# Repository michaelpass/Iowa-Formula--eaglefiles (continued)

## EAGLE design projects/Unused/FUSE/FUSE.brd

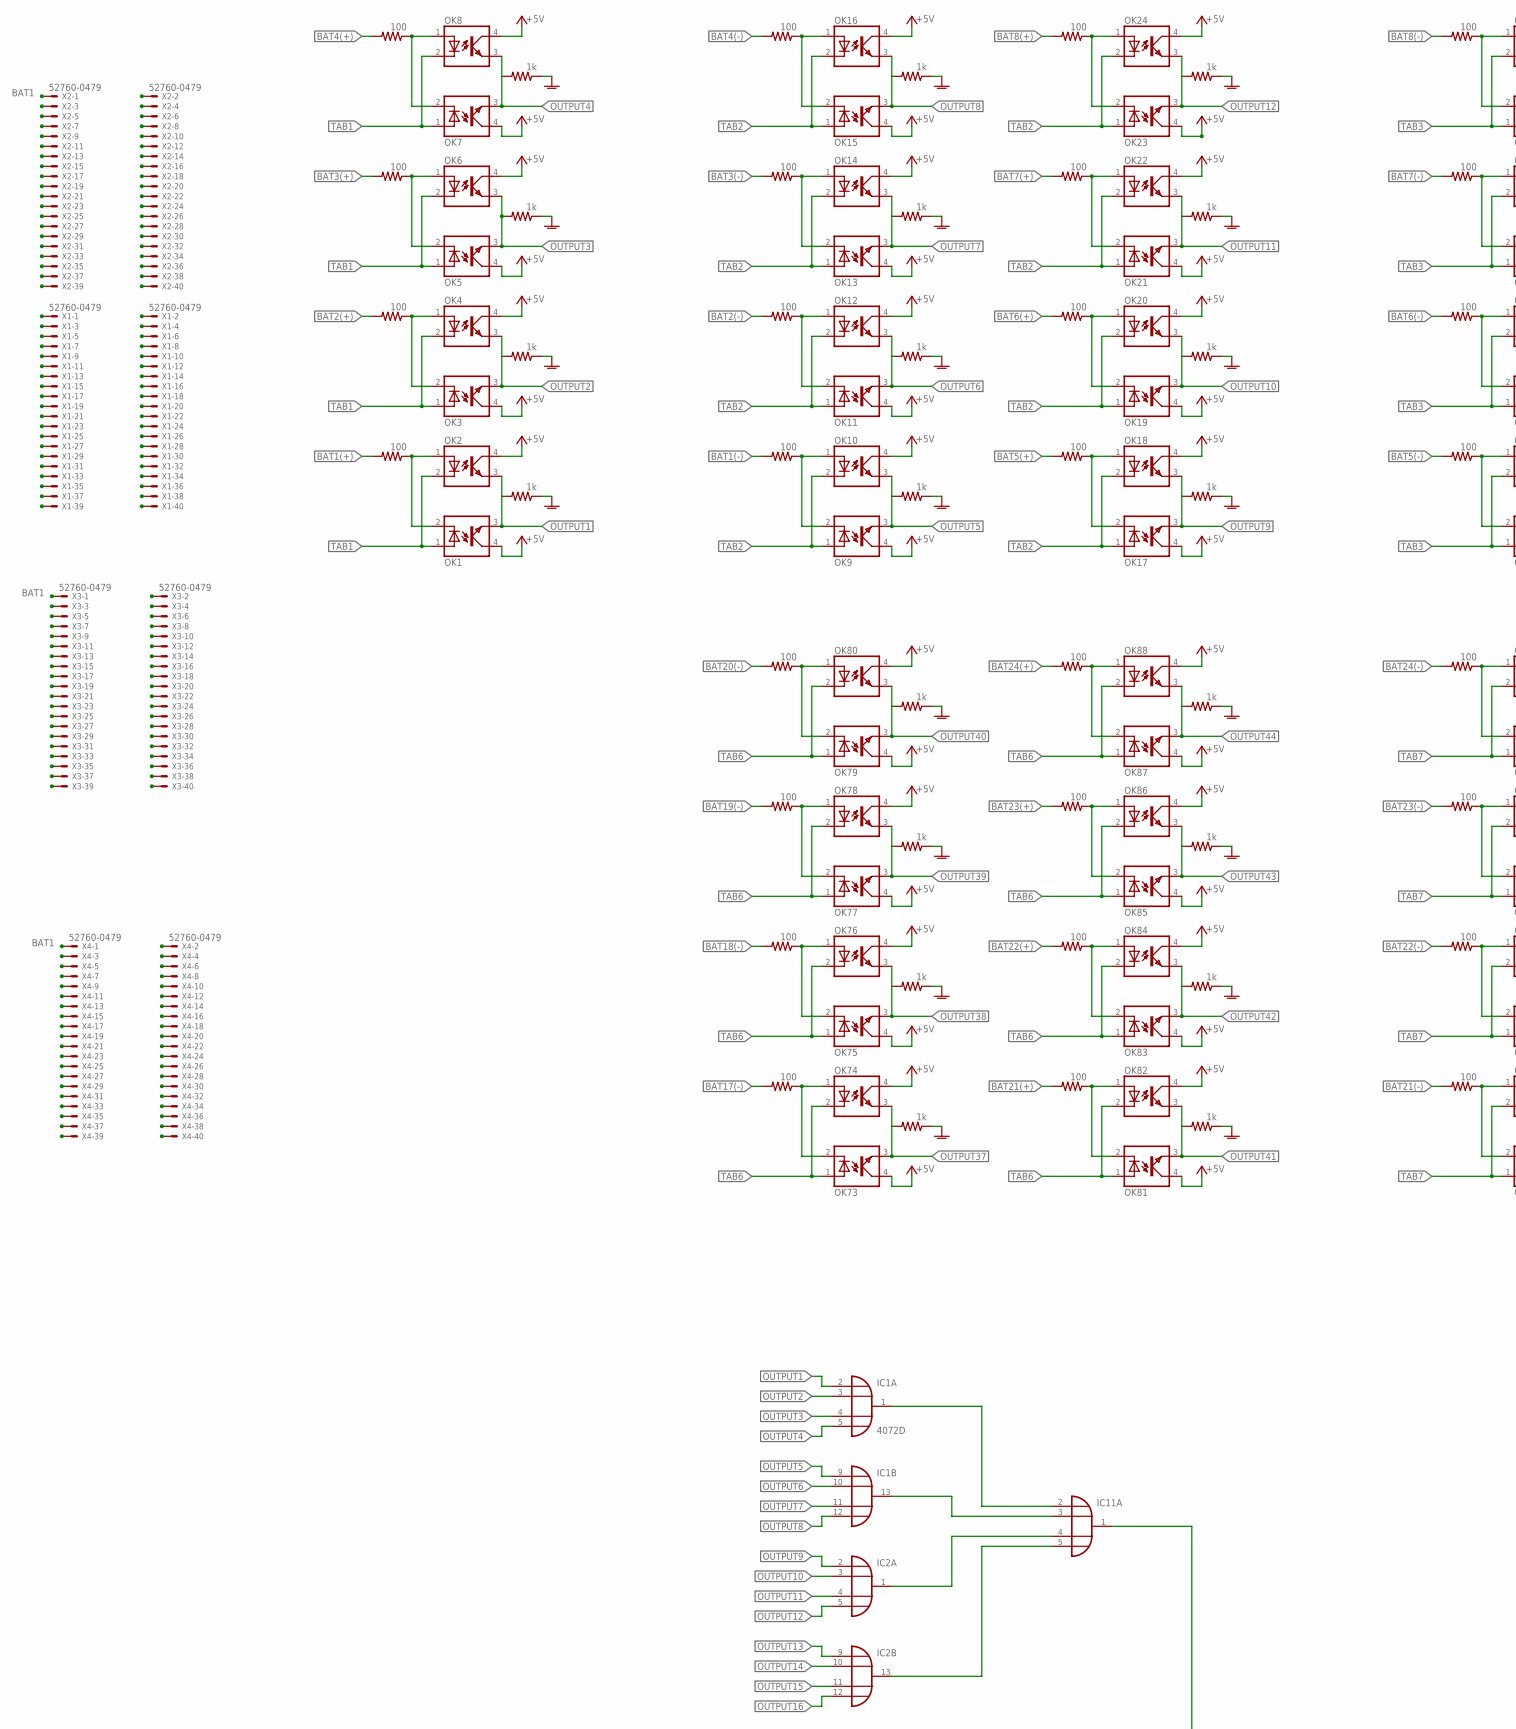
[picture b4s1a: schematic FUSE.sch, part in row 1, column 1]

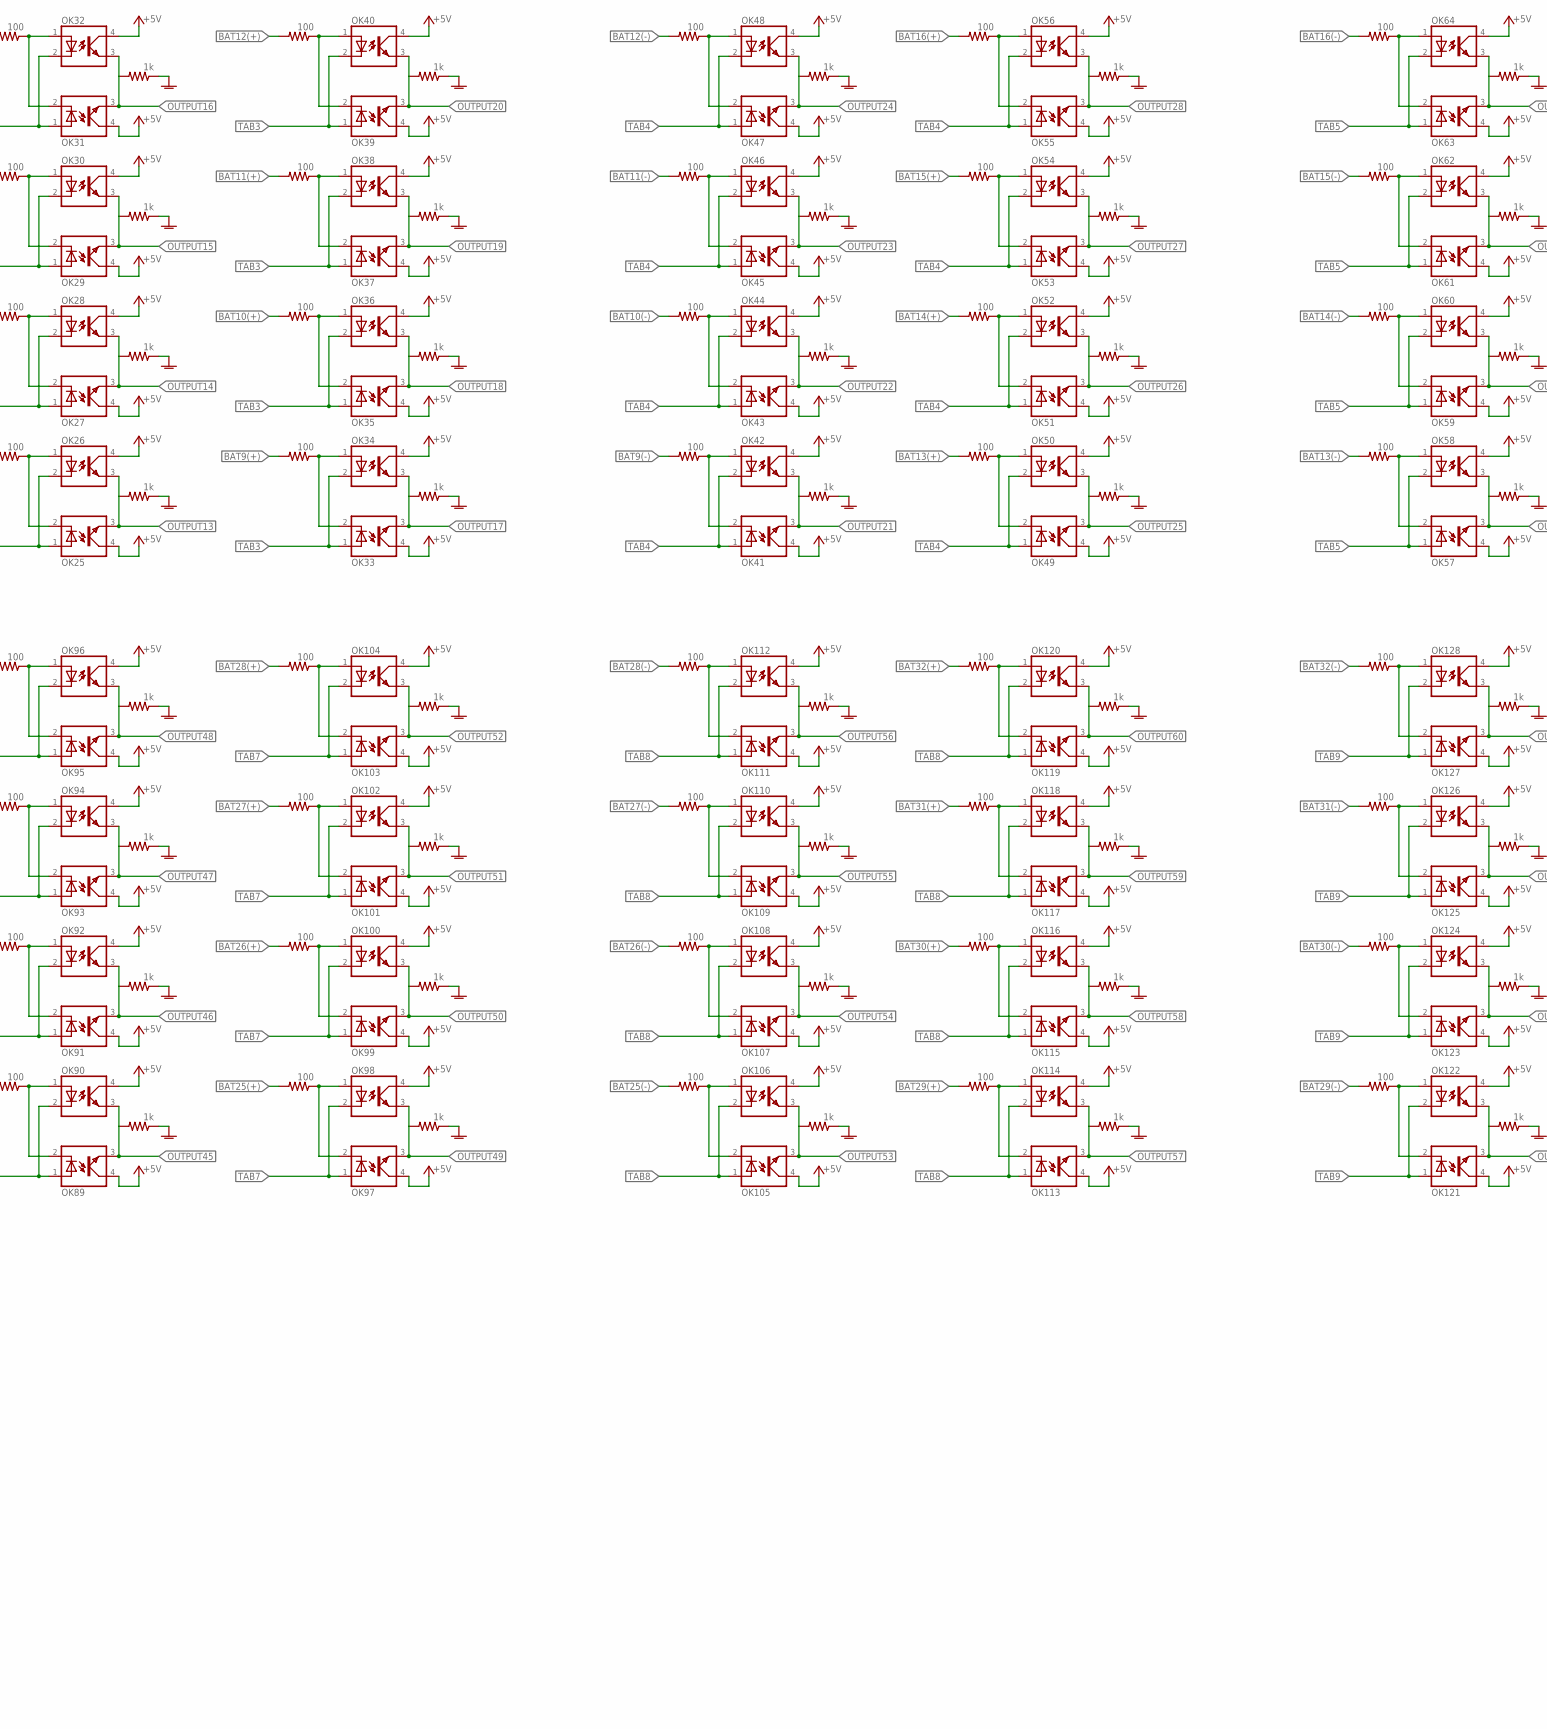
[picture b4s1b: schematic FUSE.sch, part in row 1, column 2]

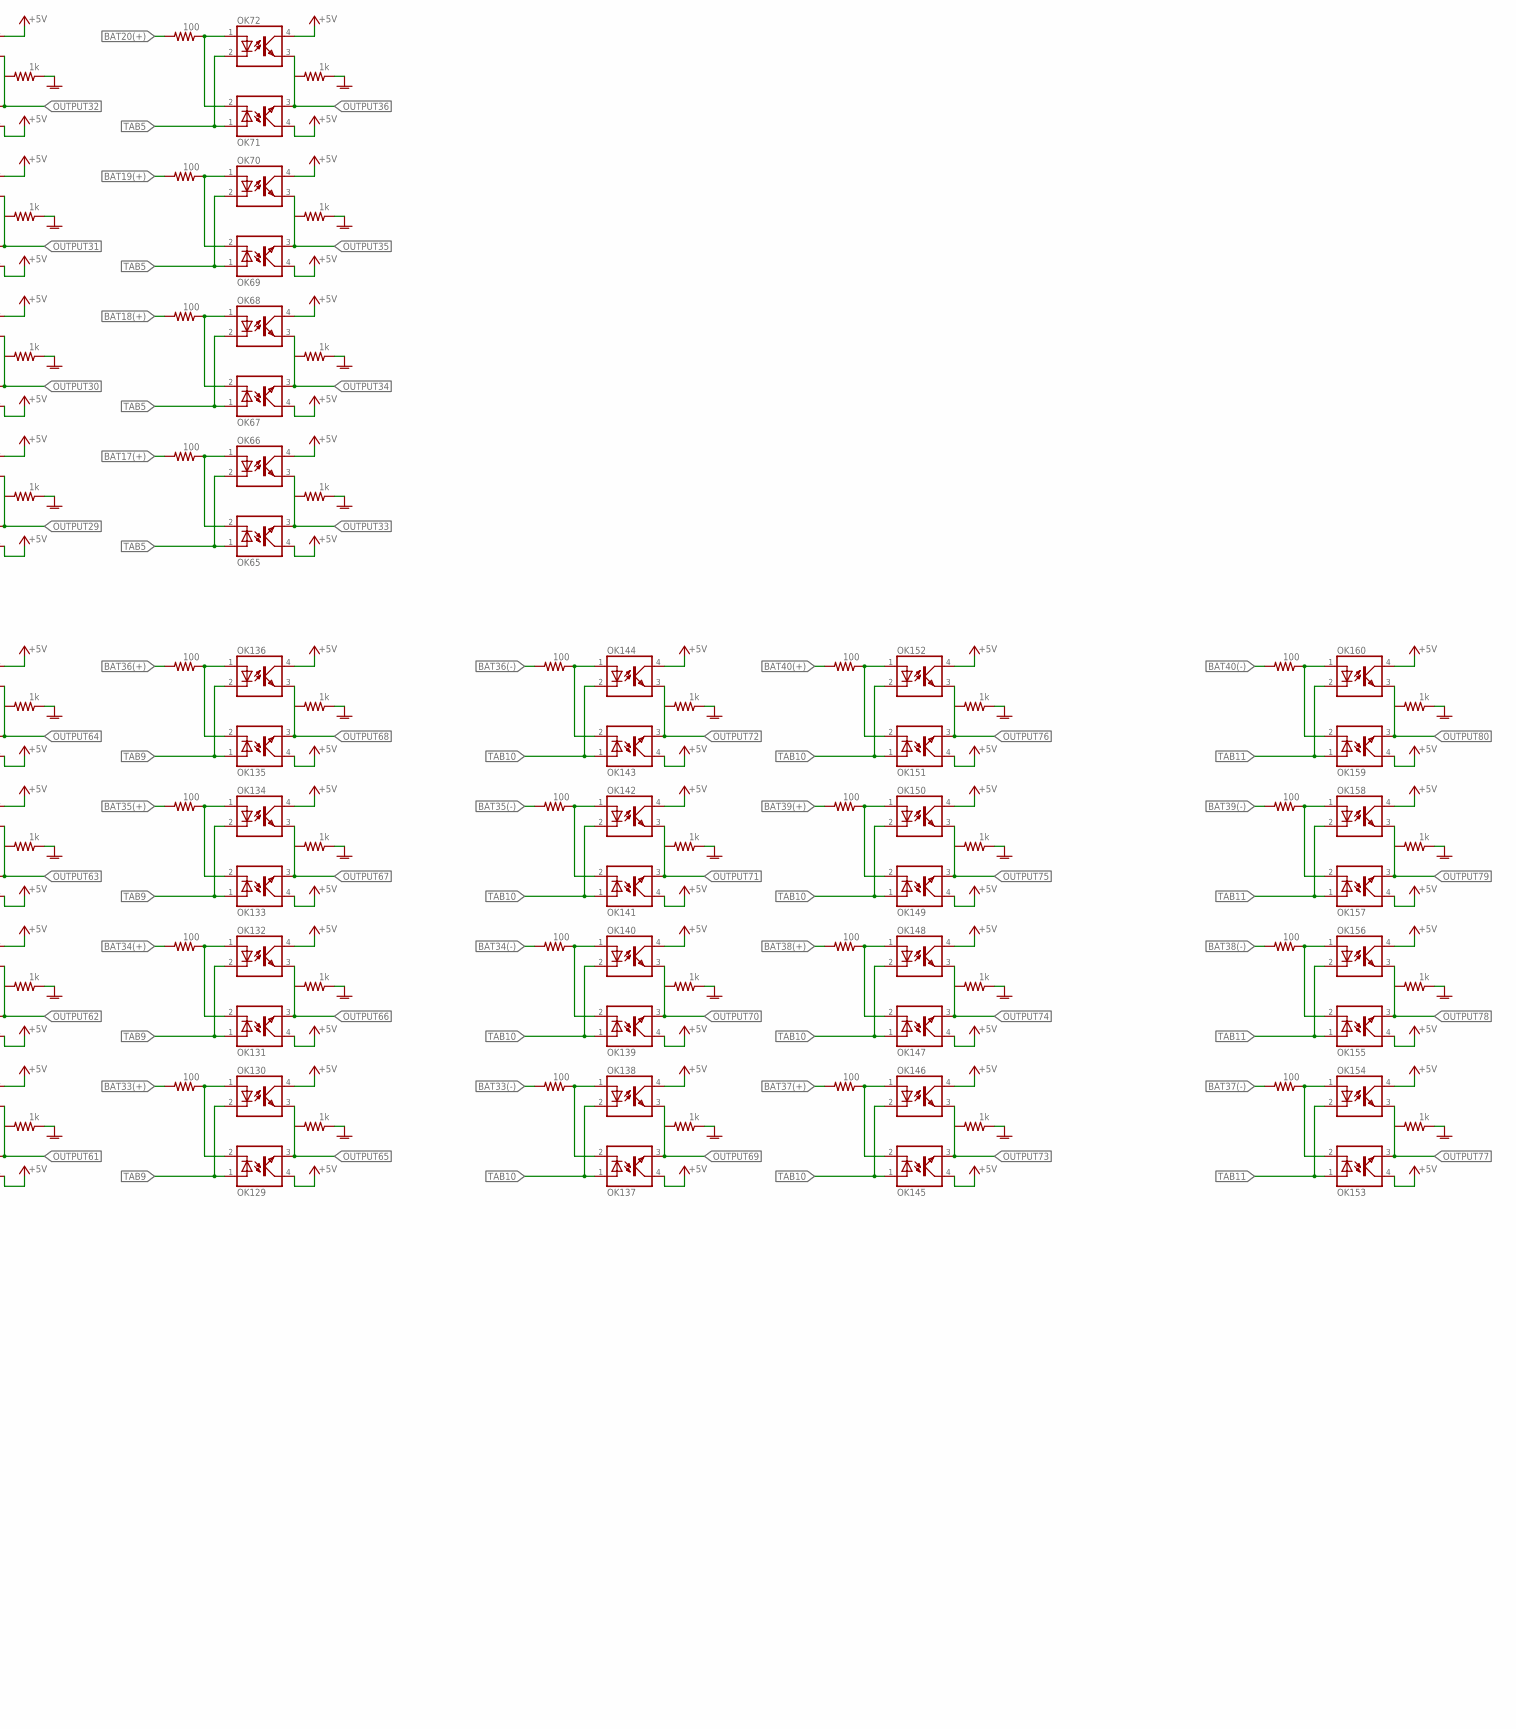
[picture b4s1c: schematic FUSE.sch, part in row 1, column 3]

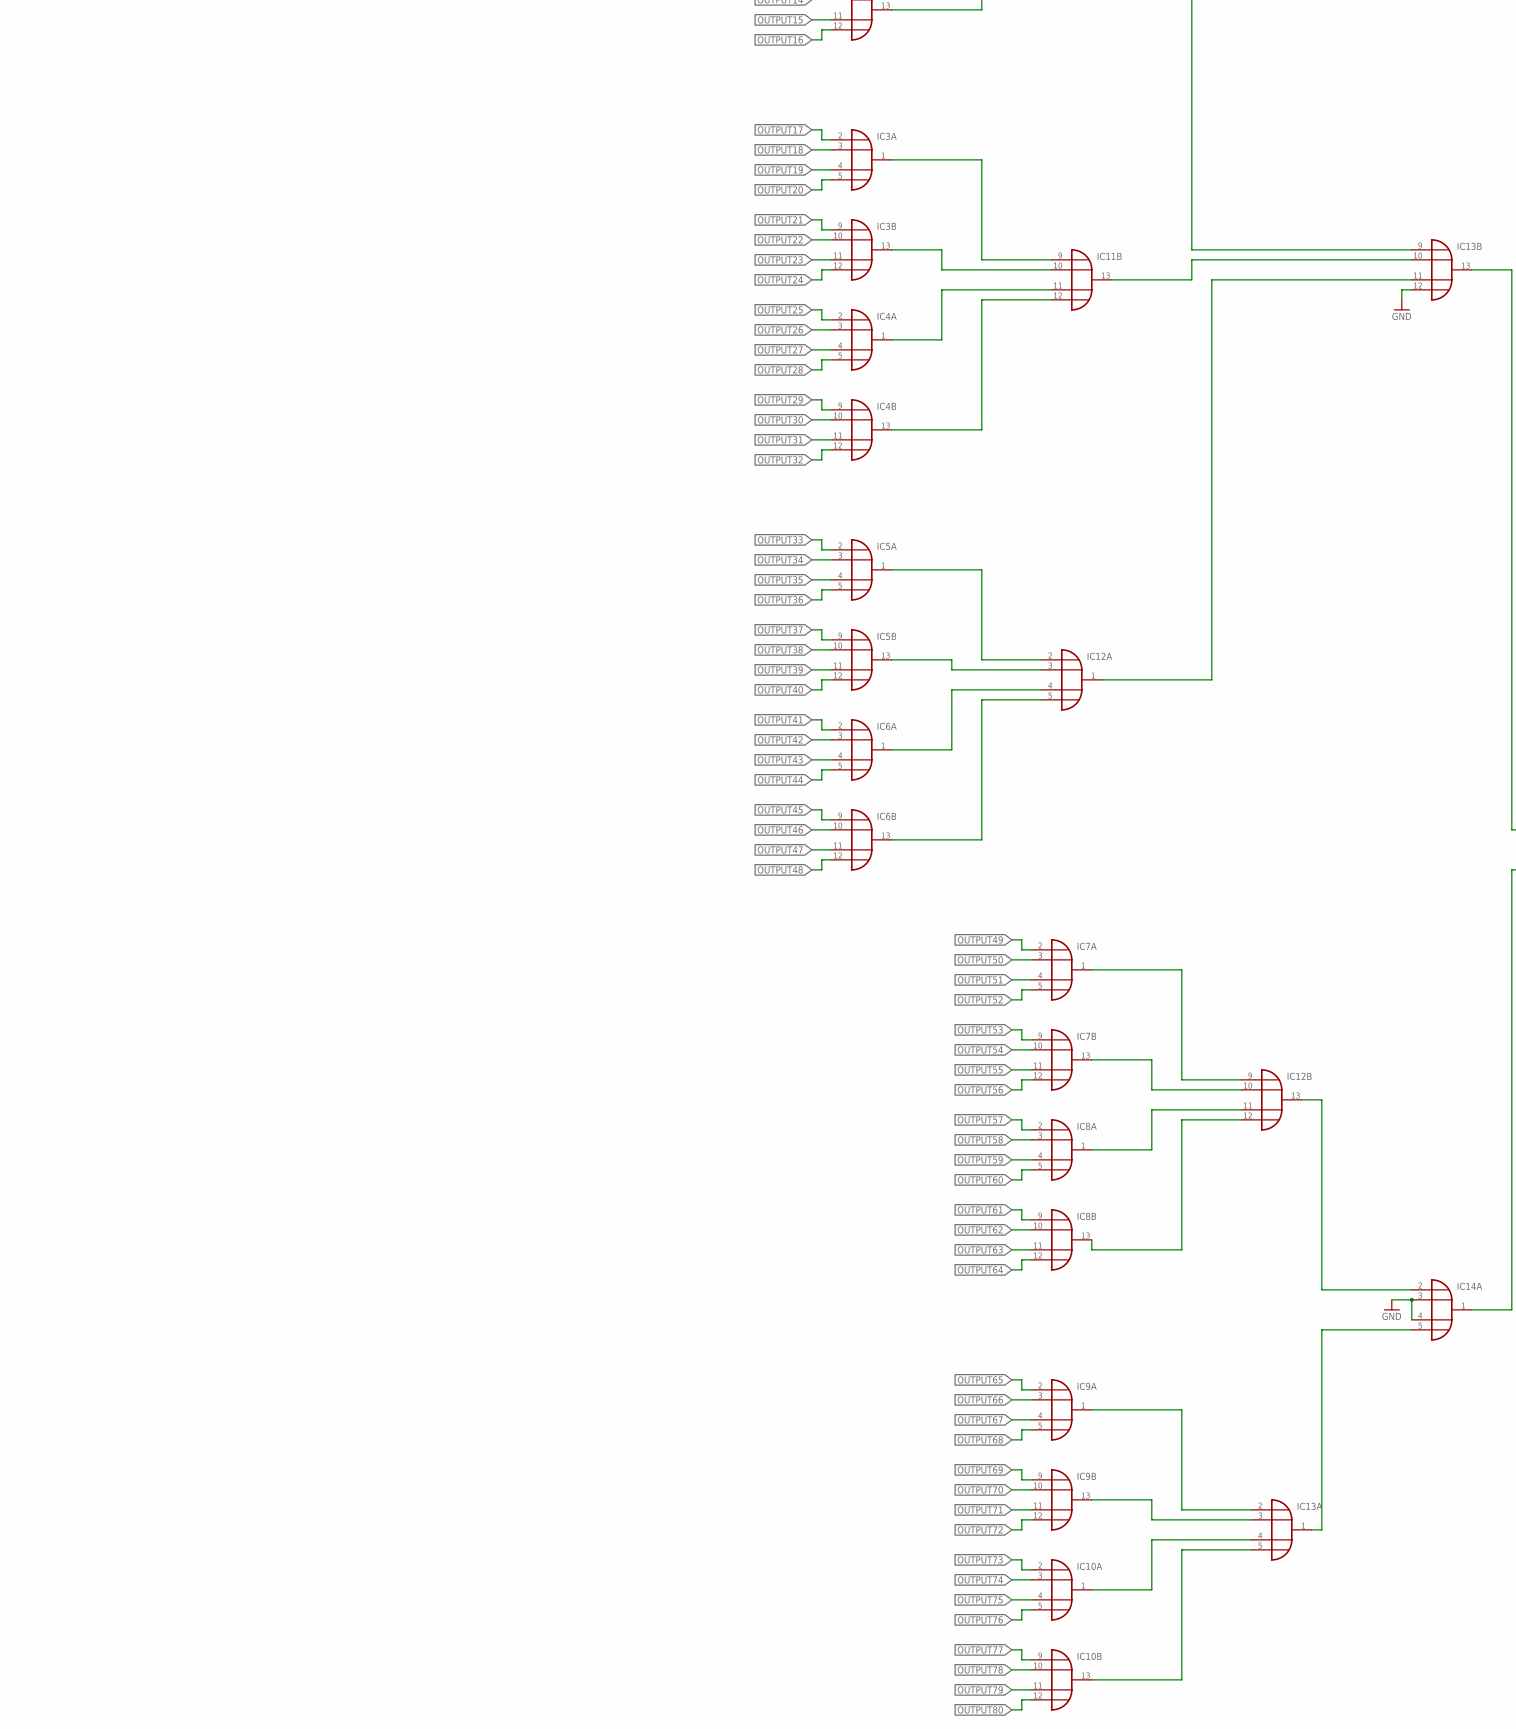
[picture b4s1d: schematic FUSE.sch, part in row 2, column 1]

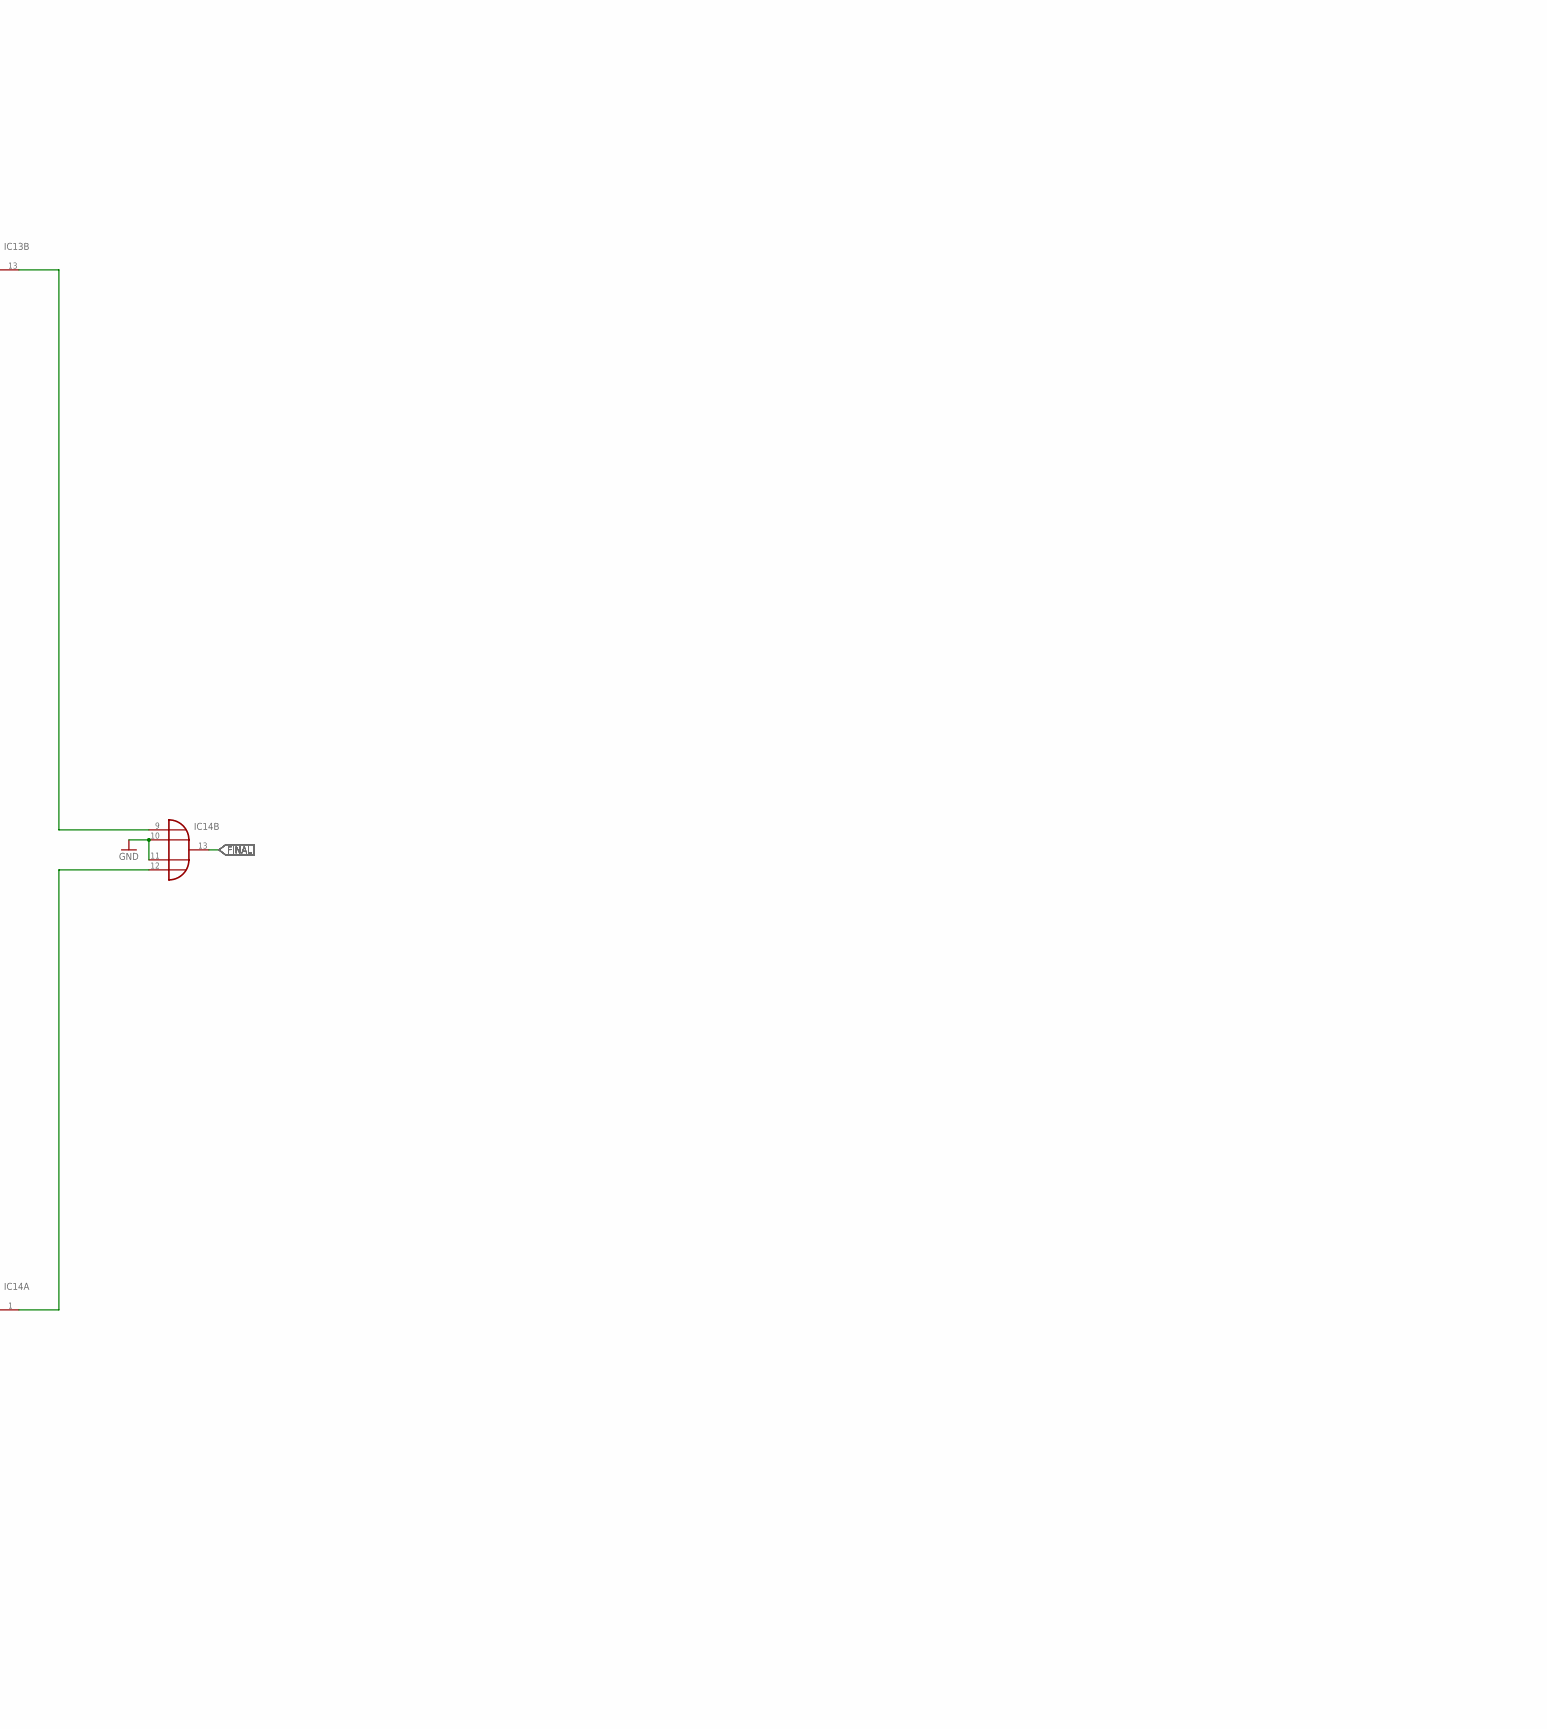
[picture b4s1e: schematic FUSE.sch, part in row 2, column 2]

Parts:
IC1, IC2, IC3, IC4, IC5, IC6, IC7, IC8, IC9, IC10, IC11, IC12, IC13, IC14: 4072D; SO14
OK1, OK2, OK3, OK4, OK5, OK6, OK7, OK8, OK9, OK10, OK11, OK12, OK13, OK14, OK15, OK16, OK17, OK18, OK19, OK20, OK21, OK22, OK23, OK24, OK25, OK26, OK27, OK28, OK29, OK30, OK31, OK32, OK33, OK34, OK35, OK36, OK37, OK38, OK39, OK40, OK41, OK42, OK43, OK44, OK45, OK46, OK47, OK48, OK49, OK50, OK51, OK52, OK53, OK54, OK55, OK56, OK57, OK58, OK59, OK60, OK61, OK62, OK63, OK64, OK65, OK66, OK67, OK68, OK69, OK70, OK71, OK72, OK73, OK74, OK75, OK76, OK77, OK78, OK79, OK80, OK81, OK82, OK83, OK84, OK85, OK86, OK87, OK88, OK89, OK90, OK91, OK92, OK93, OK94, OK95, OK96, OK97, OK98, OK99, OK100, OK101, OK102, OK103, OK104, OK105, OK106, OK107, OK108, OK109, OK110, OK111, OK112, OK113, OK114, OK115, OK116, OK117, OK118, OK119, OK120, OK121, OK122, OK123, OK124, OK125, OK126, OK127, OK128, OK129, OK130, OK131, OK132, OK133, OK134, OK135, OK136, OK137, OK138, OK139, OK140, OK141, OK142, OK143, OK144, OK145, OK146, OK147, OK148, OK149, OK150, OK151, OK152, OK153, OK154, OK155, OK156, OK157, OK158, OK159, OK160: PC817-S; SOP04(2.54)
R1, R2, R3, R4, R9, R10, R11, R12, R17, R18, R19, R20, R25, R26, R27, R28, R33, R34, R35, R36, R41, R42, R43, R44, R49, R50, R51, R52, R57, R58, R59, R60, R65, R66, R67, R68, R73, R74, R75, R76, R81, R82, R83, R84, R89, R90, R91, R92, R97, R98, R99, R100, R105, R106, R107, R108, R113, R114, R115, R116, R121, R122, R123, R124, R129, R130, R131, R132, R137, R138, R139, R140, R145, R146, R147, R148, R153, R154, R155, R156: 100; R0805
R5, R6, R7, R8, R13, R14, R15, R16, R21, R22, R23, R24, R29, R30, R31, R32, R37, R38, R39, R40, R45, R46, R47, R48, R53, R54, R55, R56, R61, R62, R63, R64, R69, R70, R71, R72, R77, R78, R79, R80, R85, R86, R87, R88, R93, R94, R95, R96, R101, R102, R103, R104, R109, R110, R111, R112, R117, R118, R119, R120, R125, R126, R127, R128, R133, R134, R135, R136, R141, R142, R143, R144, R149, R150, R151, R152, R157, R158, R159, R160: 1k; R0805
X1, X2, X3, X4: 52760-0479

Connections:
+5V: OK1.4 (COL), OK2.4 (COL), OK3.4 (COL), OK4.4 (COL), OK5.4 (COL), OK6.4 (COL), OK7.4 (COL), OK8.4 (COL), OK9.4 (COL), OK10.4 (COL), OK11.4 (COL), OK12.4 (COL), OK13.4 (COL), OK14.4 (COL), OK15.4 (COL), OK16.4 (COL), OK17.4 (COL), OK18.4 (COL), OK19.4 (COL), OK20.4 (COL), OK21.4 (COL), OK22.4 (COL), OK23.4 (COL), OK24.4 (COL), OK25.4 (COL), OK26.4 (COL), OK27.4 (COL), OK28.4 (COL), OK29.4 (COL), OK30.4 (COL), OK31.4 (COL), OK32.4 (COL), OK33.4 (COL), OK34.4 (COL), OK35.4 (COL), OK36.4 (COL), OK37.4 (COL), OK38.4 (COL), OK39.4 (COL), OK40.4 (COL), OK41.4 (COL), OK42.4 (COL), OK43.4 (COL), OK44.4 (COL), OK45.4 (COL), OK46.4 (COL), OK47.4 (COL), OK48.4 (COL), OK49.4 (COL), OK50.4 (COL), OK51.4 (COL), OK52.4 (COL), OK53.4 (COL), OK54.4 (COL), OK55.4 (COL), OK56.4 (COL), OK57.4 (COL), OK58.4 (COL), OK59.4 (COL), OK60.4 (COL), OK61.4 (COL), OK62.4 (COL), OK63.4 (COL), OK64.4 (COL), OK65.4 (COL), OK66.4 (COL), OK67.4 (COL), OK68.4 (COL), OK69.4 (COL), OK70.4 (COL), OK71.4 (COL), OK72.4 (COL), OK73.4 (COL), OK74.4 (COL), OK75.4 (COL), OK76.4 (COL), OK77.4 (COL), OK78.4 (COL), OK79.4 (COL), OK80.4 (COL), OK81.4 (COL), OK82.4 (COL), OK83.4 (COL), OK84.4 (COL), OK85.4 (COL), OK86.4 (COL), OK87.4 (COL), OK88.4 (COL), OK89.4 (COL), OK90.4 (COL), OK91.4 (COL), OK92.4 (COL), OK93.4 (COL), OK94.4 (COL), OK95.4 (COL), OK96.4 (COL), OK97.4 (COL), OK98.4 (COL), OK99.4 (COL), OK100.4 (COL), OK101.4 (COL), OK102.4 (COL), OK103.4 (COL), OK104.4 (COL), OK105.4 (COL), OK106.4 (COL), OK107.4 (COL), OK108.4 (COL), OK109.4 (COL), OK110.4 (COL), OK111.4 (COL), OK112.4 (COL), OK113.4 (COL), OK114.4 (COL), OK115.4 (COL), OK116.4 (COL), OK117.4 (COL), OK118.4 (COL), OK119.4 (COL), OK120.4 (COL), OK121.4 (COL), OK122.4 (COL), OK123.4 (COL), OK124.4 (COL), OK125.4 (COL), OK126.4 (COL), OK127.4 (COL), OK128.4 (COL), OK129.4 (COL), OK130.4 (COL), OK131.4 (COL), OK132.4 (COL), OK133.4 (COL), OK134.4 (COL), OK135.4 (COL), OK136.4 (COL), OK137.4 (COL), OK138.4 (COL), OK139.4 (COL), OK140.4 (COL), OK141.4 (COL), OK142.4 (COL), OK143.4 (COL), OK144.4 (COL), OK145.4 (COL), OK146.4 (COL), OK147.4 (COL), OK148.4 (COL), OK149.4 (COL), OK150.4 (COL), OK151.4 (COL), OK152.4 (COL), OK153.4 (COL), OK154.4 (COL), OK155.4 (COL), OK156.4 (COL), OK157.4 (COL), OK158.4 (COL), OK159.4 (COL), OK160.4 (COL)
AGND: R5.1, R6.1, R7.1, R8.1, R13.1, R14.1, R15.1, R16.1, R21.1, R22.1, R23.1, R24.1, R29.1, R30.1, R31.1, R32.1, R37.1, R38.1, R39.1, R40.1, R45.1, R46.1, R47.1, R48.1, R53.1, R54.1, R55.1, R56.1, R61.1, R62.1, R63.1, R64.1, R69.1, R70.1, R71.1, R72.1, R77.1, R78.1, R79.1, R80.1, R85.1, R86.1, R87.1, R88.1, R93.1, R94.1, R95.1, R96.1, R101.1, R102.1, R103.1, R104.1, R109.1, R110.1, R111.1, R112.1, R117.1, R118.1, R119.1, R120.1, R125.1, R126.1, R127.1, R128.1, R133.1, R134.1, R135.1, R136.1, R141.1, R142.1, R143.1, R144.1, R149.1, R150.1, R151.1, R152.1, R157.1, R158.1, R159.1, R160.1
BAT1: X2.1, X3.1, X4.1
BAT1(+): R1.2
BAT1(-): R9.2
BAT2(+): R2.2
BAT2(-): R10.2
BAT3(+): R3.2
BAT3(-): R11.2
BAT4(+): R4.2
BAT4(-): R12.2
BAT5(+): R17.2
BAT5(-): R25.2
BAT6(+): R18.2
BAT6(-): R26.2
BAT7(+): R19.2
BAT7(-): R27.2
BAT8(+): R20.2
BAT8(-): R28.2
BAT9(+): R33.2
BAT9(-): R41.2
BAT10(+): R34.2
BAT10(-): R42.2
BAT11(+): R35.2
BAT11(-): R43.2
BAT12(+): R36.2
BAT12(-): R44.2
BAT13(+): R49.2
BAT13(-): R57.2
BAT14(+): R50.2
BAT14(-): R58.2
BAT15(+): R51.2
BAT15(-): R59.2
BAT16(+): R52.2
BAT16(-): R60.2
BAT17(+): R65.2
BAT17(-): R73.2
BAT18(+): R66.2
BAT18(-): R74.2
BAT19(+): R67.2
BAT19(-): R75.2
BAT20(+): R68.2
BAT20(-): R76.2
BAT21(+): R81.2
BAT21(-): R89.2
BAT22(+): R82.2
BAT22(-): R90.2
BAT23(+): R83.2
BAT23(-): R91.2
BAT24(+): R84.2
BAT24(-): R92.2
BAT25(+): R97.2
BAT25(-): R105.2
BAT26(+): R98.2
BAT26(-): R106.2
BAT27(+): R99.2
BAT27(-): R107.2
BAT28(+): R100.2
BAT28(-): R108.2
BAT29(+): R113.2
BAT29(-): R121.2
BAT30(+): R114.2
BAT30(-): R122.2
BAT31(+): R115.2
BAT31(-): R123.2
BAT32(+): R116.2
BAT32(-): R124.2
BAT33(+): R129.2
BAT33(-): R137.2
BAT34(+): R130.2
BAT34(-): R138.2
BAT35(+): R131.2
BAT35(-): R139.2
BAT36(+): R132.2
BAT36(-): R140.2
BAT37(+): R145.2
BAT37(-): R153.2
BAT38(+): R146.2
BAT38(-): R154.2
BAT39(+): R147.2
BAT39(-): R155.2
BAT40(+): R148.2
BAT40(-): R156.2
FINAL: IC14.13 (O)
GND: IC13.12 (I3), IC14.3 (I1), IC14.4 (I2), IC14.10 (I1), IC14.11 (I2)
unnamed: OK1.2 (C), OK2.1 (A), R1.1
unnamed: IC1.1 (O), IC11.2 (I0)
unnamed: OK3.2 (C), OK4.1 (A), R2.1
unnamed: OK25.2 (C), OK26.1 (A), R25.1
unnamed: IC1.13 (O), IC11.3 (I1)
unnamed: OK5.2 (C), OK6.1 (A), R3.1
unnamed: IC2.1 (O), IC11.4 (I2)
unnamed: OK7.2 (C), OK8.1 (A), R4.1
unnamed: IC2.13 (O), IC11.5 (I3)
unnamed: IC3.1 (O), IC11.9 (I0)
unnamed: OK27.2 (C), OK28.1 (A), R26.1
unnamed: IC3.13 (O), IC11.10 (I1)
unnamed: OK29.2 (C), OK30.1 (A), R27.1
unnamed: IC4.1 (O), IC11.11 (I2)
unnamed: OK31.2 (C), OK32.1 (A), R28.1
unnamed: IC4.13 (O), IC11.12 (I3)
unnamed: OK33.2 (C), OK34.1 (A), R33.1
unnamed: IC5.1 (O), IC12.2 (I0)
unnamed: OK35.2 (C), OK36.1 (A), R34.1
unnamed: IC5.13 (O), IC12.3 (I1)
unnamed: OK37.2 (C), OK38.1 (A), R35.1
unnamed: IC6.1 (O), IC12.4 (I2)
unnamed: OK39.2 (C), OK40.1 (A), R36.1
unnamed: IC6.13 (O), IC12.5 (I3)
unnamed: OK41.2 (C), OK42.1 (A), R41.1
unnamed: IC7.1 (O), IC12.9 (I0)
unnamed: OK43.2 (C), OK44.1 (A), R42.1
unnamed: IC7.13 (O), IC12.10 (I1)
unnamed: OK45.2 (C), OK46.1 (A), R43.1
unnamed: IC8.1 (O), IC12.11 (I2)
unnamed: OK47.2 (C), OK48.1 (A), R44.1
unnamed: IC8.13 (O), IC12.12 (I3)
unnamed: OK49.2 (C), OK50.1 (A), R49.1
unnamed: IC9.1 (O), IC13.2 (I0)
unnamed: OK51.2 (C), OK52.1 (A), R50.1
unnamed: IC9.13 (O), IC13.3 (I1)
unnamed: OK53.2 (C), OK54.1 (A), R51.1
unnamed: IC10.1 (O), IC13.4 (I2)
unnamed: OK55.2 (C), OK56.1 (A), R52.1
unnamed: IC10.13 (O), IC13.5 (I3)
unnamed: OK9.2 (C), OK10.1 (A), R9.1
unnamed: IC11.1 (O), IC13.9 (I0)
unnamed: OK11.2 (C), OK12.1 (A), R10.1
unnamed: IC11.13 (O), IC13.10 (I1)
unnamed: OK13.2 (C), OK14.1 (A), R11.1
unnamed: IC12.1 (O), IC13.11 (I2)
unnamed: OK15.2 (C), OK16.1 (A), R12.1
unnamed: IC13.13 (O), IC14.9 (I0)
unnamed: OK17.2 (C), OK18.1 (A), R17.1
unnamed: IC12.13 (O), IC14.2 (I0)
unnamed: OK19.2 (C), OK20.1 (A), R18.1
unnamed: IC13.1 (O), IC14.5 (I3)
unnamed: OK21.2 (C), OK22.1 (A), R19.1
unnamed: IC14.1 (O), IC14.12 (I3)
unnamed: OK23.2 (C), OK24.1 (A), R20.1
unnamed: OK57.2 (C), OK58.1 (A), R57.1
unnamed: OK59.2 (C), OK60.1 (A), R58.1
unnamed: OK61.2 (C), OK62.1 (A), R59.1
unnamed: OK63.2 (C), OK64.1 (A), R60.1
unnamed: OK65.2 (C), OK66.1 (A), R65.1
unnamed: OK67.2 (C), OK68.1 (A), R66.1
unnamed: OK69.2 (C), OK70.1 (A), R67.1
unnamed: OK71.2 (C), OK72.1 (A), R68.1
unnamed: OK73.2 (C), OK74.1 (A), R73.1
unnamed: OK75.2 (C), OK76.1 (A), R74.1
unnamed: OK77.2 (C), OK78.1 (A), R75.1
unnamed: OK79.2 (C), OK80.1 (A), R76.1
unnamed: OK81.2 (C), OK82.1 (A), R81.1
unnamed: OK83.2 (C), OK84.1 (A), R82.1
unnamed: OK85.2 (C), OK86.1 (A), R83.1
unnamed: OK87.2 (C), OK88.1 (A), R84.1
unnamed: OK89.2 (C), OK90.1 (A), R89.1
unnamed: OK91.2 (C), OK92.1 (A), R90.1
unnamed: OK93.2 (C), OK94.1 (A), R91.1
unnamed: OK95.2 (C), OK96.1 (A), R92.1
unnamed: OK97.2 (C), OK98.1 (A), R97.1
unnamed: OK99.2 (C), OK100.1 (A), R98.1
unnamed: OK101.2 (C), OK102.1 (A), R99.1
unnamed: OK103.2 (C), OK104.1 (A), R100.1
unnamed: OK105.2 (C), OK106.1 (A), R105.1
unnamed: OK107.2 (C), OK108.1 (A), R106.1
unnamed: OK109.2 (C), OK110.1 (A), R107.1
unnamed: OK111.2 (C), OK112.1 (A), R108.1
unnamed: OK113.2 (C), OK114.1 (A), R113.1
unnamed: OK115.2 (C), OK116.1 (A), R114.1
unnamed: OK117.2 (C), OK118.1 (A), R115.1
unnamed: OK119.2 (C), OK120.1 (A), R116.1
unnamed: OK121.2 (C), OK122.1 (A), R121.1
unnamed: OK123.2 (C), OK124.1 (A), R122.1
unnamed: OK125.2 (C), OK126.1 (A), R123.1
unnamed: OK127.2 (C), OK128.1 (A), R124.1
unnamed: OK129.2 (C), OK130.1 (A), R129.1
unnamed: OK131.2 (C), OK132.1 (A), R130.1
unnamed: OK133.2 (C), OK134.1 (A), R131.1
unnamed: OK135.2 (C), OK136.1 (A), R132.1
unnamed: OK137.2 (C), OK138.1 (A), R137.1
unnamed: OK139.2 (C), OK140.1 (A), R138.1
unnamed: OK141.2 (C), OK142.1 (A), R139.1
unnamed: OK143.2 (C), OK144.1 (A), R140.1
unnamed: OK145.2 (C), OK146.1 (A), R145.1
unnamed: OK147.2 (C), OK148.1 (A), R146.1
unnamed: OK149.2 (C), OK150.1 (A), R147.1
unnamed: OK151.2 (C), OK152.1 (A), R148.1
unnamed: OK153.2 (C), OK154.1 (A), R153.1
unnamed: OK155.2 (C), OK156.1 (A), R154.1
unnamed: OK157.2 (C), OK158.1 (A), R155.1
unnamed: OK159.2 (C), OK160.1 (A), R156.1
OUTPUT1: IC1.2 (I0), OK1.3 (EMIT), OK2.3 (EMIT), R5.2
OUTPUT2: IC1.3 (I1), OK3.3 (EMIT), OK4.3 (EMIT), R6.2
OUTPUT3: IC1.4 (I2), OK5.3 (EMIT), OK6.3 (EMIT), R7.2
OUTPUT4: IC1.5 (I3), OK7.3 (EMIT), OK8.3 (EMIT), R8.2
OUTPUT5: IC1.9 (I0), OK9.3 (EMIT), OK10.3 (EMIT), R13.2
OUTPUT6: IC1.10 (I1), OK11.3 (EMIT), OK12.3 (EMIT), R14.2
OUTPUT7: IC1.11 (I2), OK13.3 (EMIT), OK14.3 (EMIT), R15.2
OUTPUT8: IC1.12 (I3), OK15.3 (EMIT), OK16.3 (EMIT), R16.2
OUTPUT9: IC2.2 (I0), OK17.3 (EMIT), OK18.3 (EMIT), R21.2
OUTPUT10: IC2.3 (I1), OK19.3 (EMIT), OK20.3 (EMIT), R22.2
OUTPUT11: IC2.4 (I2), OK21.3 (EMIT), OK22.3 (EMIT), R23.2
OUTPUT12: IC2.5 (I3), OK23.3 (EMIT), OK24.3 (EMIT), R24.2
OUTPUT13: IC2.9 (I0), OK25.3 (EMIT), OK26.3 (EMIT), R29.2
OUTPUT14: IC2.10 (I1), OK27.3 (EMIT), OK28.3 (EMIT), R30.2
OUTPUT15: IC2.11 (I2), OK29.3 (EMIT), OK30.3 (EMIT), R31.2
OUTPUT16: IC2.12 (I3), OK31.3 (EMIT), OK32.3 (EMIT), R32.2
OUTPUT17: IC3.2 (I0), OK33.3 (EMIT), OK34.3 (EMIT), R37.2
OUTPUT18: IC3.3 (I1), OK35.3 (EMIT), OK36.3 (EMIT), R38.2
OUTPUT19: IC3.4 (I2), OK37.3 (EMIT), OK38.3 (EMIT), R39.2
OUTPUT20: IC3.5 (I3), OK39.3 (EMIT), OK40.3 (EMIT), R40.2
OUTPUT21: IC3.9 (I0), OK41.3 (EMIT), OK42.3 (EMIT), R45.2
OUTPUT22: IC3.10 (I1), OK43.3 (EMIT), OK44.3 (EMIT), R46.2
OUTPUT23: IC3.11 (I2), OK45.3 (EMIT), OK46.3 (EMIT), R47.2
OUTPUT24: IC3.12 (I3), OK47.3 (EMIT), OK48.3 (EMIT), R48.2
OUTPUT25: IC4.2 (I0), OK49.3 (EMIT), OK50.3 (EMIT), R53.2
OUTPUT26: IC4.3 (I1), OK51.3 (EMIT), OK52.3 (EMIT), R54.2
OUTPUT27: IC4.4 (I2), OK53.3 (EMIT), OK54.3 (EMIT), R55.2
OUTPUT28: IC4.5 (I3), OK55.3 (EMIT), OK56.3 (EMIT), R56.2
OUTPUT29: IC4.9 (I0), OK57.3 (EMIT), OK58.3 (EMIT), R61.2
OUTPUT30: IC4.10 (I1), OK59.3 (EMIT), OK60.3 (EMIT), R62.2
OUTPUT31: IC4.11 (I2), OK61.3 (EMIT), OK62.3 (EMIT), R63.2
OUTPUT32: IC4.12 (I3), OK63.3 (EMIT), OK64.3 (EMIT), R64.2
OUTPUT33: IC5.2 (I0), OK65.3 (EMIT), OK66.3 (EMIT), R69.2
OUTPUT34: IC5.3 (I1), OK67.3 (EMIT), OK68.3 (EMIT), R70.2
OUTPUT35: IC5.4 (I2), OK69.3 (EMIT), OK70.3 (EMIT), R71.2
OUTPUT36: IC5.5 (I3), OK71.3 (EMIT), OK72.3 (EMIT), R72.2
OUTPUT37: IC5.9 (I0), OK73.3 (EMIT), OK74.3 (EMIT), R77.2
OUTPUT38: IC5.10 (I1), OK75.3 (EMIT), OK76.3 (EMIT), R78.2
OUTPUT39: IC5.11 (I2), OK77.3 (EMIT), OK78.3 (EMIT), R79.2
OUTPUT40: IC5.12 (I3), OK79.3 (EMIT), OK80.3 (EMIT), R80.2
OUTPUT41: IC6.2 (I0), OK81.3 (EMIT), OK82.3 (EMIT), R85.2
OUTPUT42: IC6.3 (I1), OK83.3 (EMIT), OK84.3 (EMIT), R86.2
OUTPUT43: IC6.4 (I2), OK85.3 (EMIT), OK86.3 (EMIT), R87.2
OUTPUT44: IC6.5 (I3), OK87.3 (EMIT), OK88.3 (EMIT), R88.2
OUTPUT45: IC6.9 (I0), OK89.3 (EMIT), OK90.3 (EMIT), R93.2
OUTPUT46: IC6.10 (I1), OK91.3 (EMIT), OK92.3 (EMIT), R94.2
OUTPUT47: IC6.11 (I2), OK93.3 (EMIT), OK94.3 (EMIT), R95.2
OUTPUT48: IC6.12 (I3), OK95.3 (EMIT), OK96.3 (EMIT), R96.2
OUTPUT49: IC7.2 (I0), OK97.3 (EMIT), OK98.3 (EMIT), R101.2
OUTPUT50: IC7.3 (I1), OK99.3 (EMIT), OK100.3 (EMIT), R102.2
OUTPUT51: IC7.4 (I2), OK101.3 (EMIT), OK102.3 (EMIT), R103.2
OUTPUT52: IC7.5 (I3), OK103.3 (EMIT), OK104.3 (EMIT), R104.2
OUTPUT53: IC7.9 (I0), OK105.3 (EMIT), OK106.3 (EMIT), R109.2
OUTPUT54: IC7.10 (I1), OK107.3 (EMIT), OK108.3 (EMIT), R110.2
OUTPUT55: IC7.11 (I2), OK109.3 (EMIT), OK110.3 (EMIT), R111.2
OUTPUT56: IC7.12 (I3), OK111.3 (EMIT), OK112.3 (EMIT), R112.2
OUTPUT57: IC8.2 (I0), OK113.3 (EMIT), OK114.3 (EMIT), R117.2
OUTPUT58: IC8.3 (I1), OK115.3 (EMIT), OK116.3 (EMIT), R118.2
OUTPUT59: IC8.4 (I2), OK117.3 (EMIT), OK118.3 (EMIT), R119.2
OUTPUT60: IC8.5 (I3), OK119.3 (EMIT), OK120.3 (EMIT), R120.2
OUTPUT61: IC8.9 (I0), OK121.3 (EMIT), OK122.3 (EMIT), R125.2
OUTPUT62: IC8.10 (I1), OK123.3 (EMIT), OK124.3 (EMIT), R126.2
OUTPUT63: IC8.11 (I2), OK125.3 (EMIT), OK126.3 (EMIT), R127.2
OUTPUT64: IC8.12 (I3), OK127.3 (EMIT), OK128.3 (EMIT), R128.2
OUTPUT65: IC9.2 (I0), OK129.3 (EMIT), OK130.3 (EMIT), R133.2
OUTPUT66: IC9.3 (I1), OK131.3 (EMIT), OK132.3 (EMIT), R134.2
OUTPUT67: IC9.4 (I2), OK133.3 (EMIT), OK134.3 (EMIT), R135.2
OUTPUT68: IC9.5 (I3), OK135.3 (EMIT), OK136.3 (EMIT), R136.2
OUTPUT69: IC9.9 (I0), OK137.3 (EMIT), OK138.3 (EMIT), R141.2
OUTPUT70: IC9.10 (I1), OK139.3 (EMIT), OK140.3 (EMIT), R142.2
OUTPUT71: IC9.11 (I2), OK141.3 (EMIT), OK142.3 (EMIT), R143.2
OUTPUT72: IC9.12 (I3), OK143.3 (EMIT), OK144.3 (EMIT), R144.2
OUTPUT73: IC10.2 (I0), OK145.3 (EMIT), OK146.3 (EMIT), R149.2
OUTPUT74: IC10.3 (I1), OK147.3 (EMIT), OK148.3 (EMIT), R150.2
OUTPUT75: IC10.4 (I2), OK149.3 (EMIT), OK150.3 (EMIT), R151.2
OUTPUT76: IC10.5 (I3), OK151.3 (EMIT), OK152.3 (EMIT), R152.2
OUTPUT77: IC10.9 (I0), OK153.3 (EMIT), OK154.3 (EMIT), R157.2
OUTPUT78: IC10.10 (I1), OK155.3 (EMIT), OK156.3 (EMIT), R158.2
OUTPUT79: IC10.11 (I2), OK157.3 (EMIT), OK158.3 (EMIT), R159.2
OUTPUT80: IC10.12 (I3), OK159.3 (EMIT), OK160.3 (EMIT), R160.2
TAB1: OK1.1 (A), OK2.2 (C), OK3.1 (A), OK4.2 (C), OK5.1 (A), OK6.2 (C), OK7.1 (A), OK8.2 (C)
TAB2: OK9.1 (A), OK10.2 (C), OK11.1 (A), OK12.2 (C), OK13.1 (A), OK14.2 (C), OK15.1 (A), OK16.2 (C), OK17.1 (A), OK18.2 (C), OK19.1 (A), OK20.2 (C), OK21.1 (A), OK22.2 (C), OK23.1 (A), OK24.2 (C)
TAB3: OK25.1 (A), OK26.2 (C), OK27.1 (A), OK28.2 (C), OK29.1 (A), OK30.2 (C), OK31.1 (A), OK32.2 (C), OK33.1 (A), OK34.2 (C), OK35.1 (A), OK36.2 (C), OK37.1 (A), OK38.2 (C), OK39.1 (A), OK40.2 (C)
TAB4: OK41.1 (A), OK42.2 (C), OK43.1 (A), OK44.2 (C), OK45.1 (A), OK46.2 (C), OK47.1 (A), OK48.2 (C), OK49.1 (A), OK50.2 (C), OK51.1 (A), OK52.2 (C), OK53.1 (A), OK54.2 (C), OK55.1 (A), OK56.2 (C)
TAB5: OK57.1 (A), OK58.2 (C), OK59.1 (A), OK60.2 (C), OK61.1 (A), OK62.2 (C), OK63.1 (A), OK64.2 (C), OK65.1 (A), OK66.2 (C), OK67.1 (A), OK68.2 (C), OK69.1 (A), OK70.2 (C), OK71.1 (A), OK72.2 (C)
TAB6: OK73.1 (A), OK74.2 (C), OK75.1 (A), OK76.2 (C), OK77.1 (A), OK78.2 (C), OK79.1 (A), OK80.2 (C), OK81.1 (A), OK82.2 (C), OK83.1 (A), OK84.2 (C), OK85.1 (A), OK86.2 (C), OK87.1 (A), OK88.2 (C)
TAB7: OK89.1 (A), OK90.2 (C), OK91.1 (A), OK92.2 (C), OK93.1 (A), OK94.2 (C), OK95.1 (A), OK96.2 (C), OK97.1 (A), OK98.2 (C), OK99.1 (A), OK100.2 (C), OK101.1 (A), OK102.2 (C), OK103.1 (A), OK104.2 (C)
TAB8: OK105.1 (A), OK106.2 (C), OK107.1 (A), OK108.2 (C), OK109.1 (A), OK110.2 (C), OK111.1 (A), OK112.2 (C), OK113.1 (A), OK114.2 (C), OK115.1 (A), OK116.2 (C), OK117.1 (A), OK118.2 (C), OK119.1 (A), OK120.2 (C)
TAB9: OK121.1 (A), OK122.2 (C), OK123.1 (A), OK124.2 (C), OK125.1 (A), OK126.2 (C), OK127.1 (A), OK128.2 (C), OK129.1 (A), OK130.2 (C), OK131.1 (A), OK132.2 (C), OK133.1 (A), OK134.2 (C), OK135.1 (A), OK136.2 (C)
TAB10: OK137.1 (A), OK138.2 (C), OK139.1 (A), OK140.2 (C), OK141.1 (A), OK142.2 (C), OK143.1 (A), OK144.2 (C), OK145.1 (A), OK146.2 (C), OK147.1 (A), OK148.2 (C), OK149.1 (A), OK150.2 (C), OK151.1 (A), OK152.2 (C)
TAB11: OK153.1 (A), OK154.2 (C), OK155.1 (A), OK156.2 (C), OK157.1 (A), OK158.2 (C), OK159.1 (A), OK160.2 (C)
VDD: IC1.14 (VDD), IC2.14 (VDD), IC3.14 (VDD), IC4.14 (VDD), IC5.14 (VDD), IC6.14 (VDD), IC7.14 (VDD), IC8.14 (VDD), IC9.14 (VDD), IC10.14 (VDD), IC11.14 (VDD), IC12.14 (VDD), IC13.14 (VDD), IC14.14 (VDD)
VSS: IC1.7 (VSS), IC2.7 (VSS), IC3.7 (VSS), IC4.7 (VSS), IC5.7 (VSS), IC6.7 (VSS), IC7.7 (VSS), IC8.7 (VSS), IC9.7 (VSS), IC10.7 (VSS), IC11.7 (VSS), IC12.7 (VSS), IC13.7 (VSS), IC14.7 (VSS)

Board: 2 copper layers, 338 parts (4 on the bottom side), 204 nets, no tracks yet.
